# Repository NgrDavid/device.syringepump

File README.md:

## Harp Syringe Pump
This is a repository for the Harp Syringe Pump. The Harp Syringe Pump is a device that can be used to control the flow of liquid through a syringe by driving a stepper motor.

### Key Features ###

* Low and High-level interface control of the stepper motor
* General digital inputs configurable to trigger hardware events
* Digital outputs configurable to report hardware events
* Includes on-board stepper-motor driver
* Included mechanical designs and assembly instructions

### Connectivity ###

* 1x clock sync input (CLKIN) [stereo jack]
* 1x USB (for computer) [USB type B]
* 1x 12V supply [barrel connector jack]
* General purpose I/O (5V) [screw terminal]

## Interface ##

The interface with the Harp Behavior can be done through [Bonsai](https://bonsai-rx.org/) or a dedicated GUI (Graphical User Interface).

## Licensing ##

Each subdirectory will contain a license or, possibly, a set of licenses if it involves both hardware and software.

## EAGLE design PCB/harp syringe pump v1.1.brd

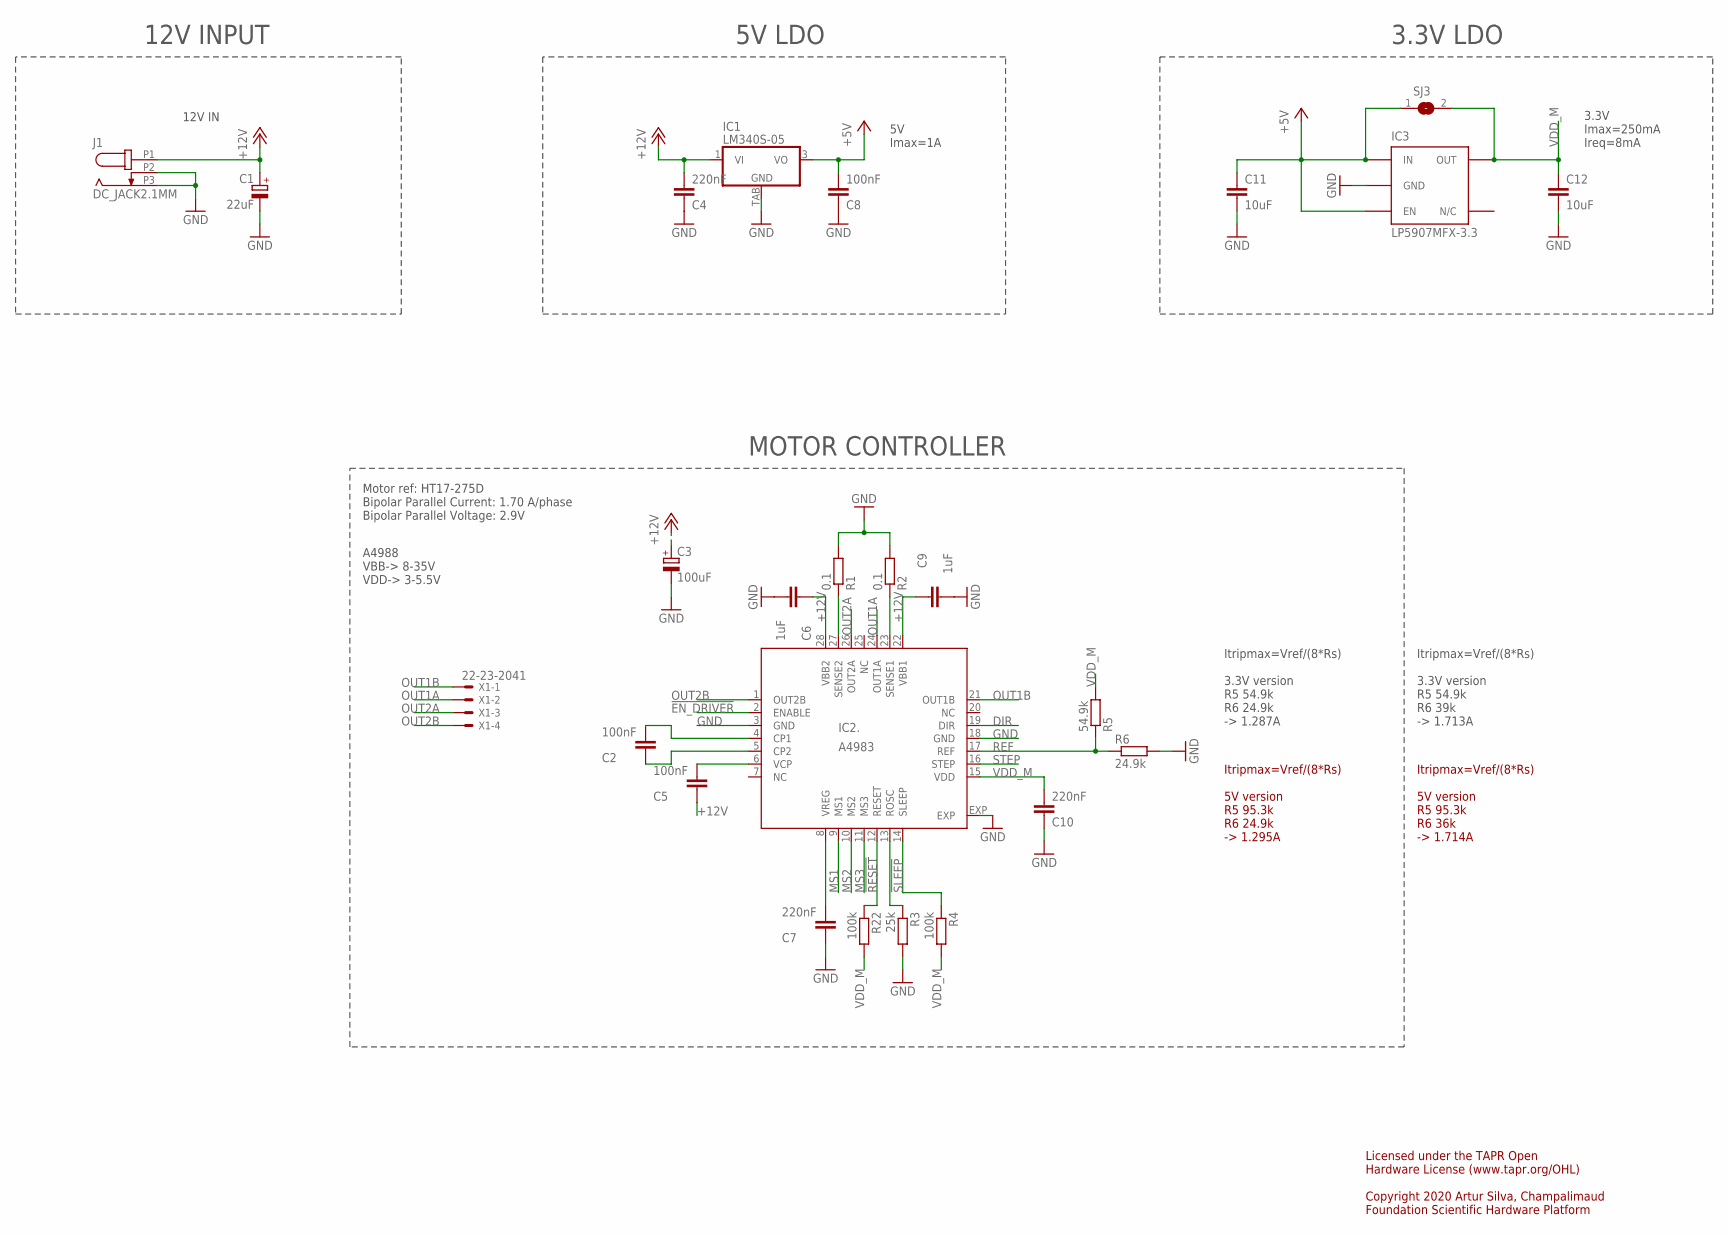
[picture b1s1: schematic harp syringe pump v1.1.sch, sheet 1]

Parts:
C1: 22uF; CAP_100UF_HAND
C2, C5: 100nF; C0603
C3: 100uF; PANASONIC_E
C4, C7, C10: 220nF; C0603
C6, C9: 1uF; C0603
C8: 100nF; C0402
C11, C12: 10uF; C0603
IC1: LM340S-05; TO263-3
IC2.: A4983; QFN28ET
IC3: LP5907MFX-3.3; TSOT23-5
J1: DC_JACK2.1MM; DC_POWER_INPUT_2.1MM
R1, R2: 0.1; R2010
R3: 25k; R0402
R4, R22: 100k; R0402
R5: 54.9k; R0402
R6: 24.9k; R0402
SJ3: SJ
X1: 22-23-2041

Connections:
!EN_DRIVER: IC2..2 (ENABLE); also elsewhere on the board
!RESET: IC2..12 (RESET), R22.1; also elsewhere on the board
!SLEEP: IC2..14 (SLEEP), R4.1; also elsewhere on the board
+5V: C8.2, C11.1, IC1.3 (VO), IC3.1 (IN), IC3.3 (EN), SJ3.1; also elsewhere on the board
+12V: C1.+, C3.+, C4.2, C5.1, C6.1, C9.1, IC1.1 (VI), IC2..22 (VBB1), IC2..28 (VBB2), J1.P1 (1)
CP1: C2.2, IC2..4 (CP1)
CP2: C2.1, IC2..5 (CP2)
DIR: IC2..19 (DIR); also elsewhere on the board
GND: C1.-, C3.-, C4.1, C6.2, C7.1, C8.1, C9.2, C10.1, C11.2, C12.2, IC1.TAB (GND), IC2..3 (GND), IC2..18 (GND), IC2..EXP, IC3.2 (GND), J1.P2 (2), J1.P3 (3), R1.2, R2.2, R3.2, R6.2; also elsewhere on the board
MS1: IC2..9 (MS1); also elsewhere on the board
MS2: IC2..10 (MS2); also elsewhere on the board
MS3: IC2..11 (MS3); also elsewhere on the board
unnamed: C7.2, IC2..8 (VREG)
unnamed: IC2..13 (ROSC), R3.1
OUT1A: IC2..24 (OUT1A), X1.2
OUT1B: IC2..21 (OUT1B), X1.1
OUT2A: IC2..26 (OUT2A), X1.3
OUT2B: IC2..1 (OUT2B), X1.4
REF: IC2..17 (REF), R5.1, R6.1
SENSE1: IC2..23 (SENSE1), R2.1
SENSE2: IC2..27 (SENSE2), R1.1
STEP: IC2..16 (STEP); also elsewhere on the board
VCP: C5.2, IC2..6 (VCP)
VDD_M: C10.2, C12.1, IC2..15 (VDD), IC3.5 (OUT), R4.2, R5.2, R22.2, SJ3.2

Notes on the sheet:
Licensed under the TAPR Open Hardware License (www.tapr.org/OHL) Copyright 2020 Artur Silva, Champalimaud Foundation Scientific Hardware Platform
12V IN
3.3V Imax=250mA Ireq=8mA
MOTOR CONTROLLER
Motor ref: HT17-275D Bipolar Parallel Current: 1.70 A/phase Bipolar Parallel Voltage: 2.9V
5V LDO
3.3V LDO
12V INPUT
A4988 VBB-> 8-35V VDD-> 3-5.5V
5V Imax=1A
Itripmax=Vref/(8*Rs) 3.3V version R5 54.9k R6 24.9k -> 1.287A
Itripmax=Vref/(8*Rs) 5V version R5 95.3k R6 24.9k -> 1.295A
Itripmax=Vref/(8*Rs) 5V version R5 95.3k R6 36k -> 1.714A
Itripmax=Vref/(8*Rs) 3.3V version R5 54.9k R6 39k -> 1.713A

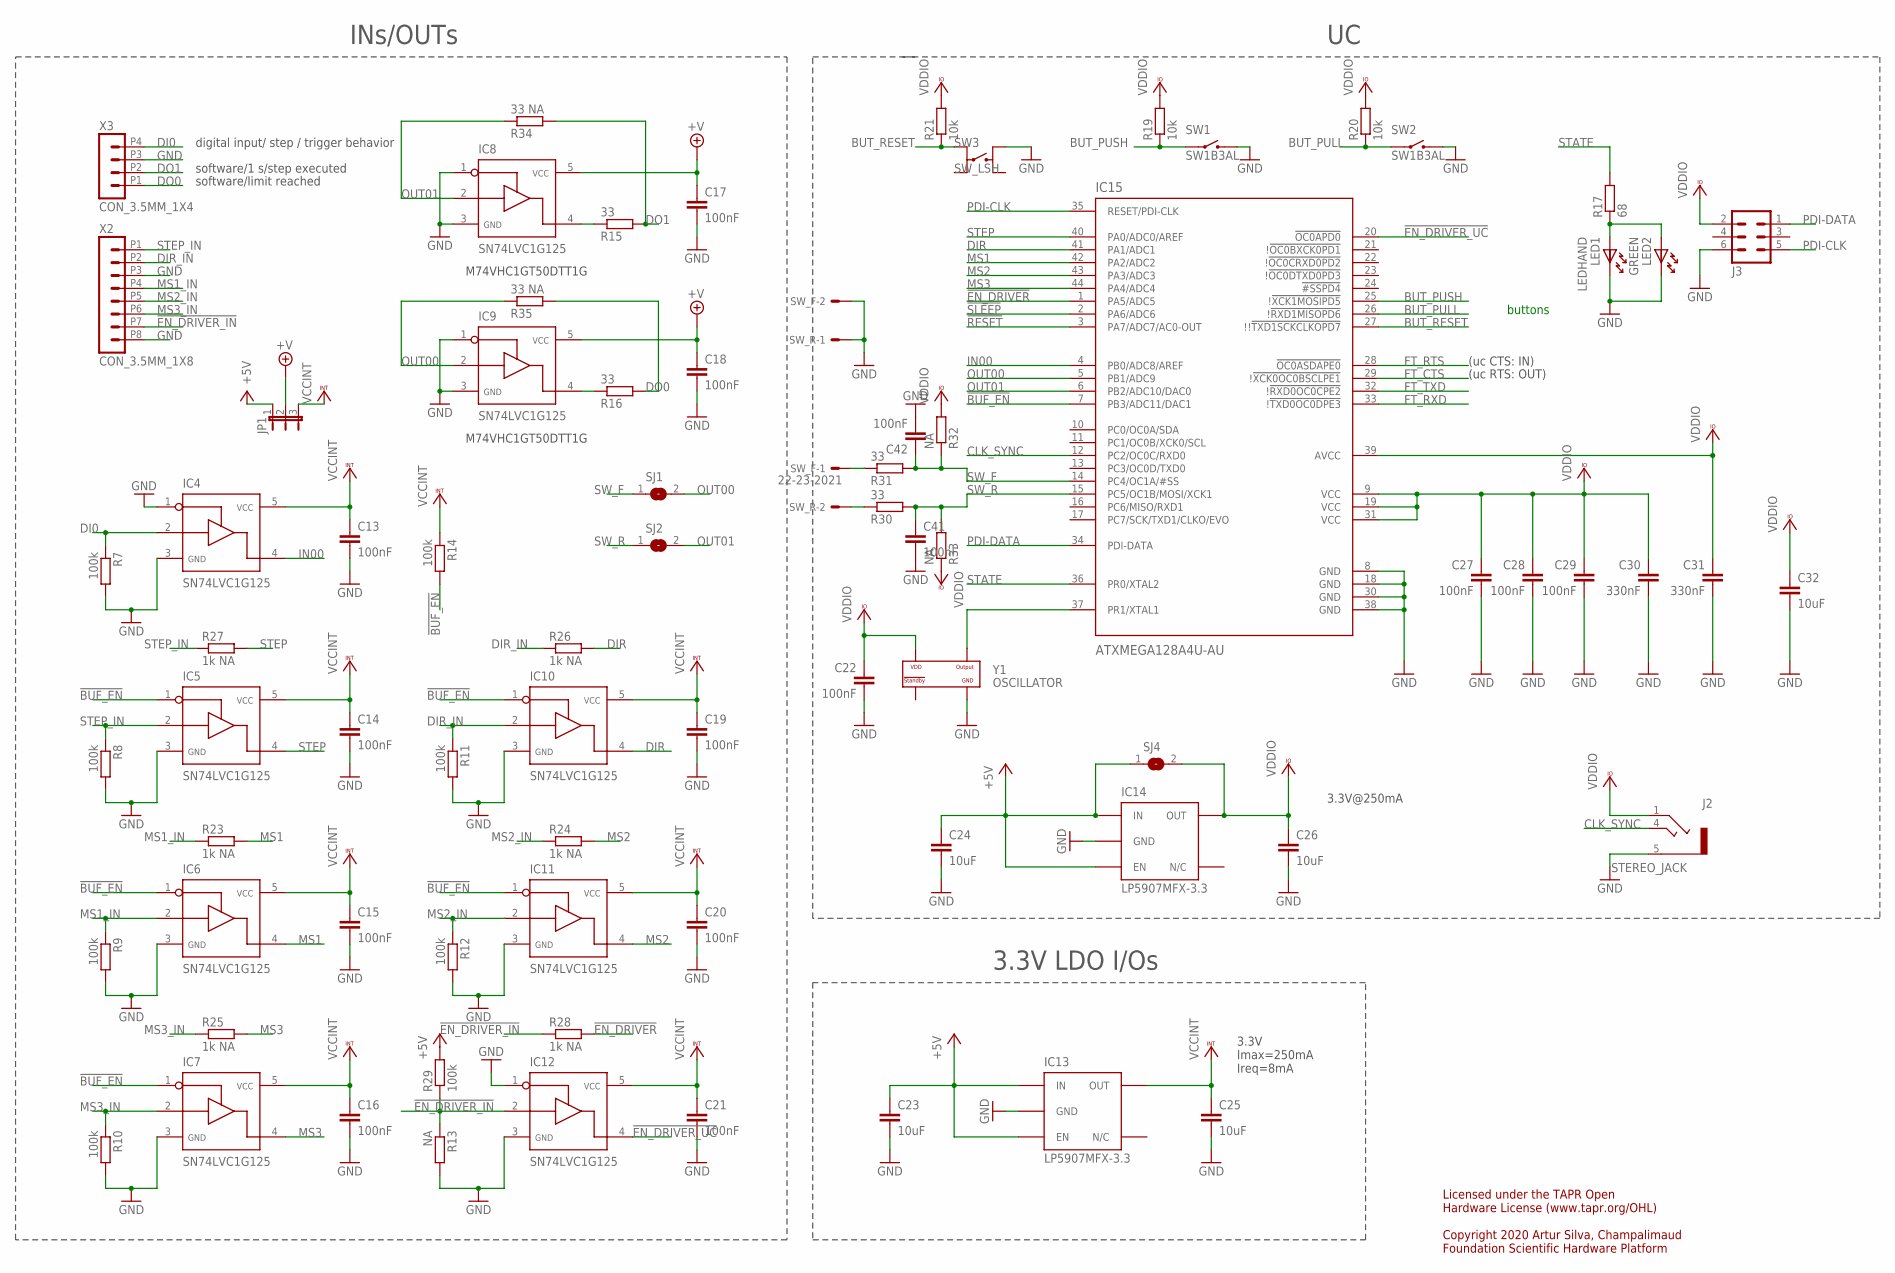
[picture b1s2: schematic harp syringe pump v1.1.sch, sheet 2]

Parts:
C13, C14, C15, C16, C17, C18, C19, C20, C21, C22, C27, C28, C29, C41, C42: 100nF; C0402
C23, C24, C25, C26, C32: 10uF; C0603
C30, C31: 330nF; C0402
IC4, IC5, IC6, IC7, IC8, IC9, IC10, IC11, IC12: SN74LVC1G125; SOT23-5
IC13, IC14: LP5907MFX-3.3; TSOT23-5
IC15: ATXMEGA128A4U-AU; QFP80P1200X1200X120-44N
J2: STEREO_JACK; 35RASMT2BHNTRX
J3: MA03-2
JP1: JP2E; JP2
LED1: LEDHAND; LED_HAND
LED2: GREEN; LED_HAND
R7, R8, R9, R10, R11, R12, R14, R29: 100k; R0402
R13, R32, R33: NA; R0402
R15, R16, R30, R31: 33; R0402
R17: 68; R0402
R19, R20, R21: 10k; R0402
R23, R24, R25, R26, R27, R28: 1k NA; R0402
R34, R35: 33 NA; R0402
SJ1, SJ2, SJ4: SJ
SW1, SW2: SW1B3AL; SW_B3AL
SW3: SW_LSH; SWITCH_LSH
SW_F: 22-23-2021
SW_R: 22-23-2021
X2: CON_3.5MM_1X8
X3: CON_3.5MM_1X4
Y1: OSCILLATOR; OSCILLATOR_3.2X2.5

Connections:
!BUF_EN: IC5.1, IC6.1, IC7.1, IC10.1, IC11.1, IC15.7 (PB3/ADC11/DAC1), R14.2
!EN_DRIVER: IC15.1 (PA5/ADC5), R28.2; also elsewhere on the board
!EN_DRIVER_IN: IC12.2, R13.1, R28.1, R29.1, X2.P7 (7)
!EN_DRIVER_UC: IC12.4, IC15.20 (!OC0APD0)
!RESET: IC15.3 (PA7/ADC7/AC0-OUT); also elsewhere on the board
!SLEEP: IC15.2 (PA6/ADC6); also elsewhere on the board
+5V: C23.1, C24.1, IC13.1 (IN), IC13.3 (EN), IC14.1 (IN), IC14.3 (EN), JP1.1, R29.2, SJ4.1; also elsewhere on the board
+V: C17.1, C18.1, IC8.5, IC9.5, JP1.2
BUT_PULL: IC15.26 (!!RXD1MISOPD6), R20.1, SW2.P
BUT_PUSH: IC15.25 (!!XCK1MOSIPD5), R19.1, SW1.P
BUT_RESET: IC15.27 (!!!TXD1SCKCLKOPD7), R21.1, SW3.P0
CLK_SYNC: IC15.12 (PC2/OC0C/RXD0), J2.4
DI0: IC4.2, R7.1, X3.P4 (4)
DIR: IC10.4, IC15.41 (PA1/ADC1), R26.2; also elsewhere on the board
DIR_IN: IC10.2, R11.1, R26.1, X2.P2 (2)
DO0: R16.2, R35.2, X3.P1 (1)
DO1: R15.2, R34.2, X3.P2 (2)
FT_CTS: IC15.29 (!!XCK0OC0BSCLPE1); also elsewhere on the board
FT_RTS: IC15.28 (!OC0ASDAPE0); also elsewhere on the board
FT_RXD: IC15.33 (!!TXD0OC0DPE3); also elsewhere on the board
FT_TXD: IC15.32 (!!RXD0OC0CPE2); also elsewhere on the board
GND: C13.2, C14.2, C15.2, C16.2, C17.2, C18.2, C19.2, C20.2, C21.2, C22.2, C23.2, C24.2, C25.2, C26.2, C27.2, C28.2, C29.2, C30.2, C31.2, C32.2, C41.2, C42.2, IC4.1, IC4.3, IC5.3, IC6.3, IC7.3, IC8.1, IC8.3, IC9.1, IC9.3, IC10.3, IC11.3, IC12.1, IC12.3, IC13.2 (GND), IC14.2 (GND), IC15.8 (GND), IC15.18 (GND), IC15.30 (GND), IC15.38 (GND), J2.5, J3.6, LED1.K, LED2.K, R7.2, R8.2, R9.2, R10.2, R11.2, R12.2, R13.2, SW1.O, SW2.O, SW3.O0 (O), SW_F.2, SW_R.1, X2.P3 (3), X2.P8 (8), X3.P3 (3), Y1.P$2 (GND); also elsewhere on the board
IN00: IC4.4, IC15.4 (PB0/ADC8/AREF)
MS1: IC6.4, IC15.42 (PA2/ADC2), R23.2; also elsewhere on the board
MS1_IN: IC6.2, R9.1, R23.1, X2.P4 (4)
MS2: IC11.4, IC15.43 (PA3/ADC3), R24.2; also elsewhere on the board
MS2_IN: IC11.2, R12.1, R24.1, X2.P5 (5)
MS3: IC7.4, IC15.44 (PA4/ADC4), R25.2; also elsewhere on the board
MS3_IN: IC7.2, R10.1, R25.1, X2.P6 (6)
unnamed: IC8.4, R15.1
unnamed: R30.1, SW_R.2
unnamed: R31.1, SW_F.1
unnamed: IC9.4, R16.1
unnamed: LED1.A, LED2.A, R17.1
OSC1: IC15.37 (PR1/XTAL1), Y1.P$3 (OUTPUT)
OUT00: IC9.2, IC15.5 (PB1/ADC9), R35.1, SJ1.2
OUT01: IC8.2, IC15.6 (PB2/ADC10/DAC0), R34.1, SJ2.2
PDI-CLK: IC15.35 (RESET/PDI-CLK), J3.5
PDI-DATA: IC15.34 (PDI-DATA), J3.1
STATE: IC15.36 (PR0/XTAL2), R17.2
STEP: IC5.4, IC15.40 (PA0/ADC0/AREF), R27.2; also elsewhere on the board
STEP_IN: IC5.2, R8.1, R27.1, X2.P1 (1)
SW_F: C42.1, IC15.14 (PC4/OC1A/#SS), R31.2, R32.1, SJ1.1
SW_R: C41.1, IC15.15 (PC5/OC1B/MOSI/XCK1), R30.2, R33.2, SJ2.1
VCCINT: C13.1, C14.1, C15.1, C16.1, C19.1, C20.1, C21.1, C25.1, IC4.5, IC5.5, IC6.5, IC7.5, IC10.5, IC11.5, IC12.5, IC13.5 (OUT), JP1.3, R14.1
VCCIO: C22.1, C26.1, C27.1, C28.1, C29.1, C30.1, C31.1, C32.1, IC14.5 (OUT), IC15.9 (VCC), IC15.19 (VCC), IC15.31 (VCC), IC15.39 (AVCC), J2.1, J3.2, R19.2, R20.2, R21.2, R32.2, R33.1, SJ4.2, Y1.P$4 (VDD)

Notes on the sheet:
3.3V@250mA
(uc CTS: IN)
(uc RTS: OUT)
buttons
M74VHC1GT50DTT1G
INs/OUTs
digital input/ step / trigger behavior
software/1 s/step executed
software/limit reached
3.3V Imax=250mA Ireq=8mA
3.3V LDO I/Os
Licensed under the TAPR Open Hardware License (www.tapr.org/OHL) Copyright 2020 Artur Silva, Champalimaud Foundation Scientific Hardware Platform

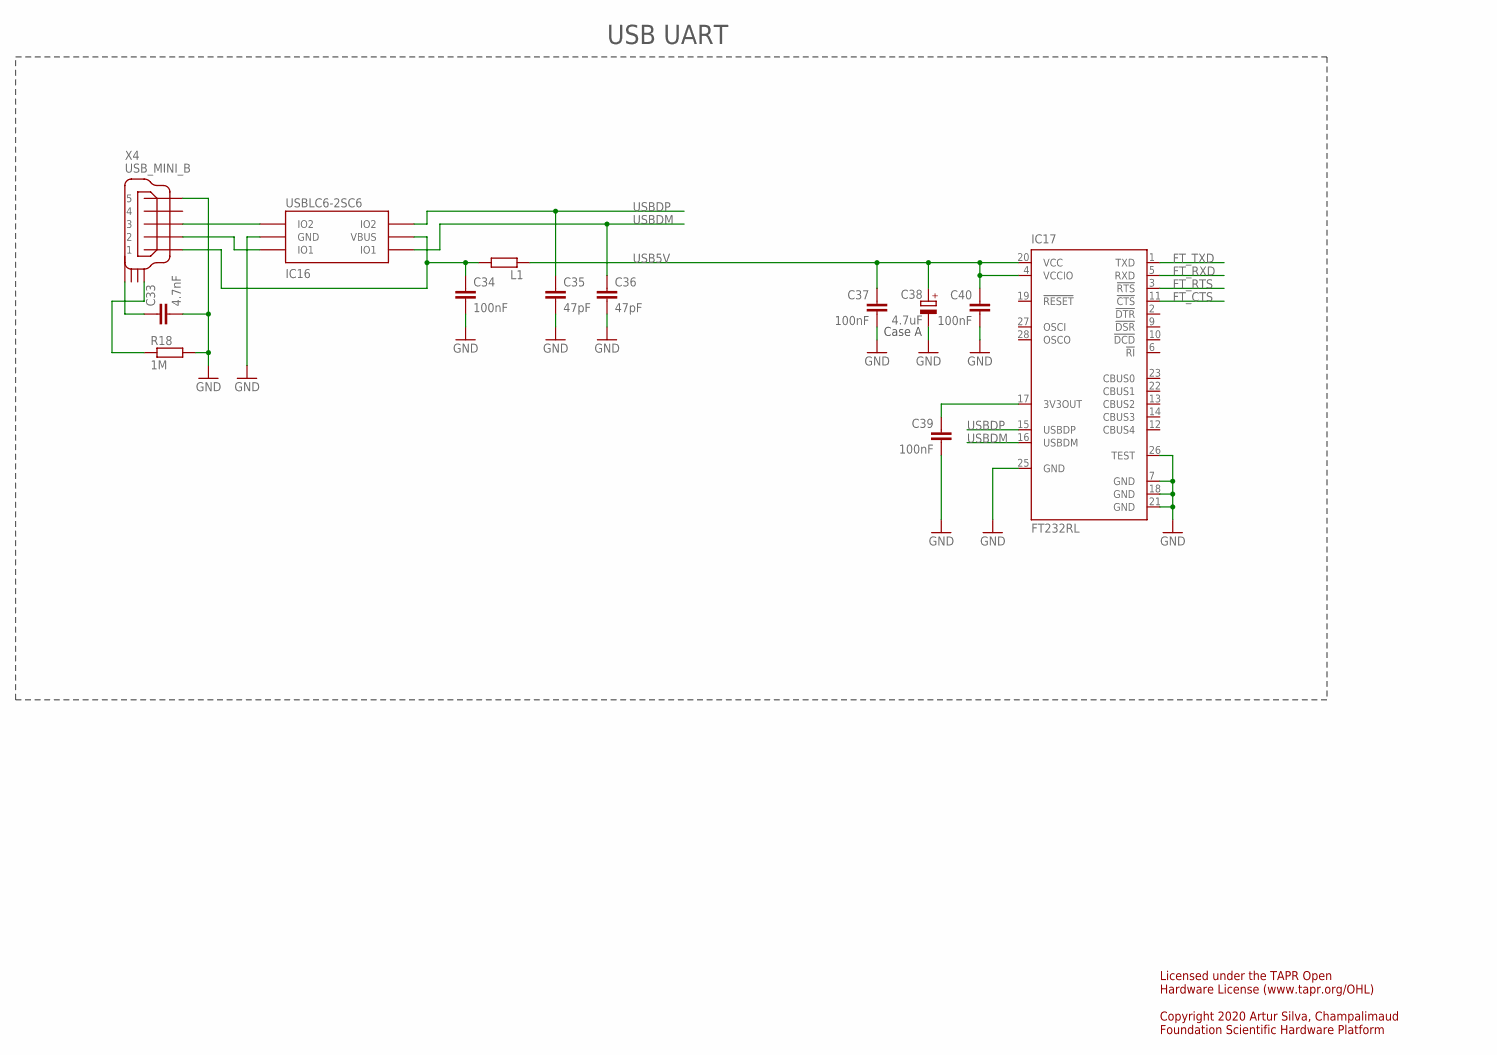
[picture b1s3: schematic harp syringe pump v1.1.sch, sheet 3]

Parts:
C33: 4.7nF; C0402
C34, C37, C39, C40: 100nF; C0402
C35, C36: 47pF; C0402
C38: 4.7uF; A/3216-18W
IC16: USBLC6-2SC6; SOT23-6L
IC17: FT232RL; SSOP28
L1: ???; R0805
R18: 1M; R0402
X4: USB_MINI_B; 240-0002-1

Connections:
3V3OUT: C39.1, IC17.17 (3V3OUT)
FT_CTS: IC17.11 (!CTS); also elsewhere on the board
FT_RTS: IC17.3 (!RTS); also elsewhere on the board
FT_RXD: IC17.5 (RXD); also elsewhere on the board
FT_TXD: IC17.1 (TXD); also elsewhere on the board
GND: C33.2, C34.2, C35.2, C36.2, C37.2, C38.-, C39.2, C40.2, IC16.P$2 (GND), IC17.7 (GND), IC17.18 (GND), IC17.21 (GND), IC17.25 (GND), IC17.26 (TEST), R18.2, X4.P$5 (5); also elsewhere on the board
unnamed: IC16.P$3 (IO2), X4.P$3 (3)
unnamed: C33.1, X4.SHIELD_4
unnamed: C34.1, IC16.P$5 (VBUS), L1.2, X4.P$1 (1)
unnamed: R18.1, X4.SHIELD_1
unnamed: IC16.P$1 (IO1), X4.P$2 (2)
USB5V: C37.1, C38.+, C40.1, IC17.4 (VCCIO), IC17.20 (VCC), L1.1
USBDM: C36.1, IC16.P$6 (IO1), IC17.16 (USBDM)
USBDP: C35.1, IC16.P$4 (IO2), IC17.15 (USBDP)

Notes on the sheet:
Case A
USB UART
Licensed under the TAPR Open Hardware License (www.tapr.org/OHL) Copyright 2020 Artur Silva, Champalimaud Foundation Scientific Hardware Platform

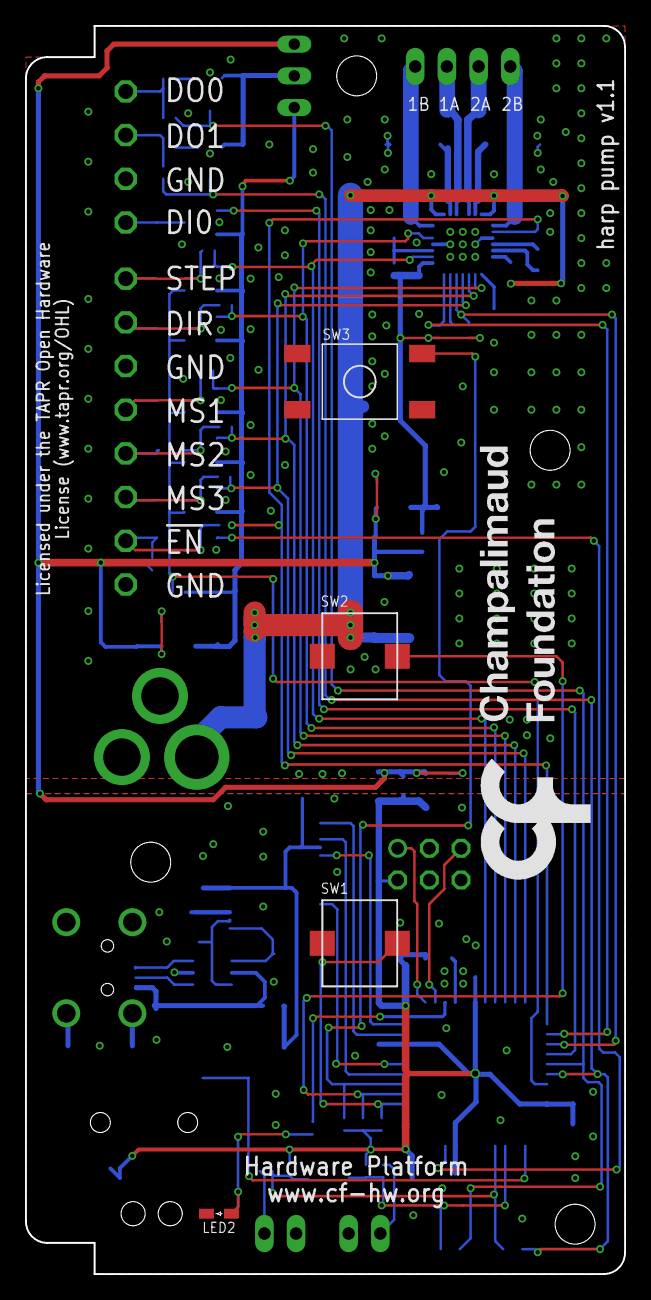
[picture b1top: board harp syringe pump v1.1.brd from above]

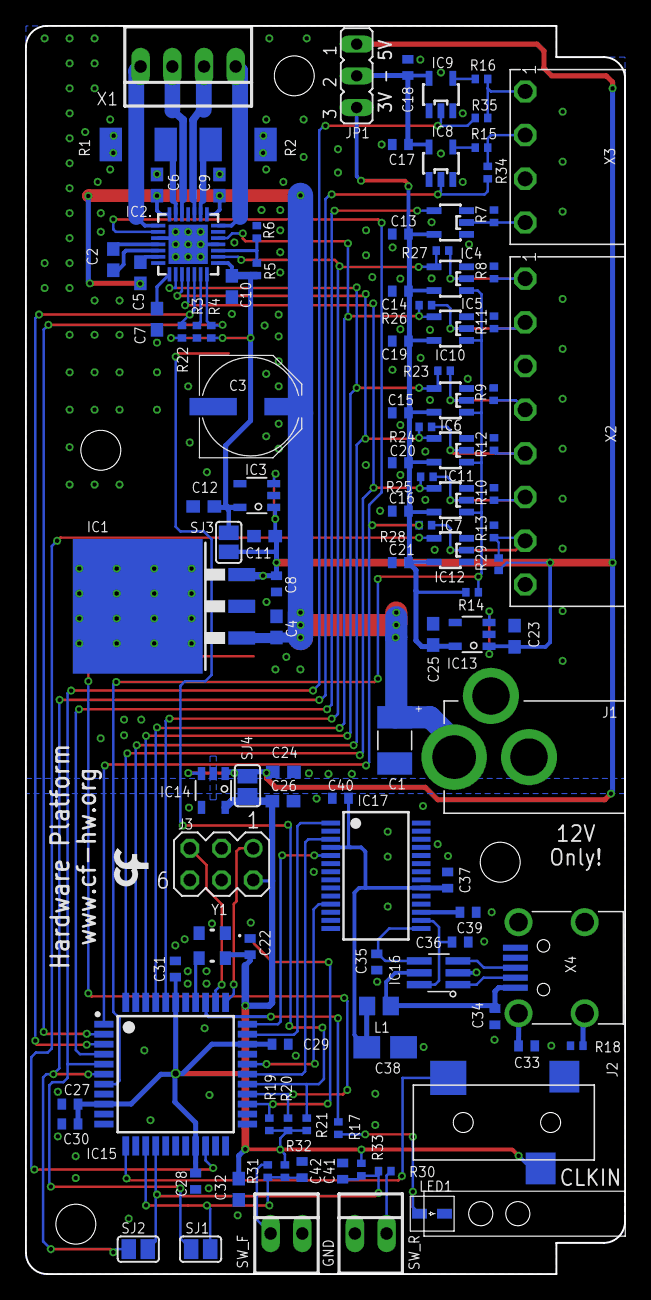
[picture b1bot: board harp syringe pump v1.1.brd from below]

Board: 2 copper layers, 48.0 x 100.0 mm, 118 parts (113 on the bottom side), 69 nets.

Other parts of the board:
U$2: LOGO_5
U$3: LED_PIPE_7513D2-L
U$4: LOGO_8

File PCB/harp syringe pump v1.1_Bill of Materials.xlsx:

| Part(s) | Quantity Low Level | Quantity Full | Description | Distributor | Part. No.
 | IC1 | 1 | 1 | Reguladores de tensão linear 3-TERMINAL POS REG 5V 1A | Mouser | 926-LM340S-5.0/NOPB |  | Low Level Only Bold
 | IC2 | 1 | 1 | DMOS Microstepping Driver with Translator and Overcurrent Protection IC | Farnell | 2057418
 | IC3, IC13, IC14 | 0 | 3 | LDO 250mA Ultra-Lo Noise LDO Reg | Mouser | 595-LP5907MFX-3.3NPB
 | IC4, IC5, IC6, IC7, IC10, IC11, IC12 | 0 | 7 | SingleBuffer / Driver, 1.65V to 5.5V, SOT-23-5 | Mouser | 595-SN74LVC1G125DBVR
 | IC8, IC9 | 0 | 2 | Buffers e line drivers 1.65-5.5V Single Non-Inverting TTL | Mouser | 863-M74VHC1GT50DTT1G
 | IC15 | 0 | 1 | Microcontroladores de 8 bits - MCU 44TQFP, IND TEMP GREEN, 1.6-3.6V | Mouser | 556-ATXMEGA128A4U-AU
 | IC16 | 0 | 1 | ESD Protection Low Cap | Mouser | 511-USBLC6-2SC6Y
 | IC17 | 0 | 1 | IC USB USB to Serial UART Enhanced IC SSOP-28 | Mouser | 895-FT232RL
 | C35, C36 | 0 | 2 | CAP CER 47pF 50V ±5% C0G 0402 | Mouser | 77-VJ0402A470JXACBC
 | C33 | 0 | 1 | CAP CER 4.7nF 100V ±10% X7R 0402 | Mouser | 81-GRM155R72A472KA01
 | C13, C14, C15, C16, C17, C18, C19, C20, C21, C22, C27, C28, C29, C34, C37, C39,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 | 2 | 19 | CAP CER 100nF 10V ±10% X5R 0402 | Farnell | 2310530
 | C2, C5, C8 | 3 | 3 | CAP CER 100nF 100V ±10% X7R 0402 | Mouser | 81-GRM188R72A104KA35
 | C4, C7, C10 | 3 | 3 | CAP CER 220nF 100V ±10% X7R 0603 | Mouser | 81-GCM188R71H224KA4J
 | C30, C31 | 0 | 2 | CAP CER 330nF 10V ±10% X5R 0402 | Digikey | CL05A334KP5NNNC
 | C6, C9 | 2 | 2 | CAP CER 1uF 25V ±20% X5R 0603 | Mouser | 581-06033D105K
 | C38 | 0 | 1 | CAP TAN 4.7uF 10V ±10% 1206 | Mouser | 80-T491A475K107280
 | C11, C12, C23, C24, C25, C26, C32 | 1 | 7 | CAP CER 10uF 35V ±20% X5R 0603 | Mouser | 81-GRM188R6YA106MA3D
 | C1 | 1 | 1 | CAP TAN 22uF 20V ±10% 1210 | Mouser | 667-20TQC22MYFB
 | C3 | 1 | 1 | CAP ELE 100uF 25V ±20% | Mouser | 667-EEE-FK1E101P
 | R1, R2 | 2 | 2 | RES SMD 0.1Ω 1% 2010 1W | Mouser | 652-CRM2010FXR100ELF
 | R15, R16, R30, R31 | 2 | 4 | RES SMD 33Ω ±5% 0402 | Mouser | 667-ERJ-2GEJ330X
 | R34, R35 | 2 | 0 | RES SMD 33Ω ±5% 0402 | Mouser | 667-ERJ-2GEJ330X
 | R17 | 0 | 1 | RES SMD 68Ω 5% 0402 | Mouser | 71-CRCW0402-68-E3
 | R23, R24, R25, R26, R27, R28 | 6 | 0 | RES SMD 1kΩ 1% 0402 | Mouser | 667-ERJ-2RKF1001X
 | R19, R20, R21 | 0 | 3 | RES SMD 10kΩ 1% 0402 | Mouser | 667-ERJ-2RKF1002X
 | R32, R33 | 2 | 0 | RES SMD 10kΩ 1% 0402 | Mouser | 667-ERJ-2RKF1002X
 | R3 | 1 | 1 | RES SMD 24.9kΩ 1% 0402 | Mouser | 667-ERJ-2RKF2492X
 | R6 | 0 | 1 | RES SMD 39kΩ 1% 0402 | Mouser | 667-ERJ-2RKF3902X
 | R6 | 1 | 0 | RES SMD 36kΩ 1% 0402 | Mouser | 667-ERJ-2RKF3602X
 | R5 | 0 | 1 | RES SMD 54.9kΩ 1% 0402 | Mouser | 667-ERJ-U02F5492X
 | R5 | 1 | 0 | RES SMD 95.3kΩ 1% 0402 | Mouser | ERJ-U02F9532X
 | R4, R7, R8, R9, R10, R11, R12, R14, R22, R29 | 2 | 10 | RES SMD 100kΩ ±1% 0402 | Mouser | 667-ERJ-2RKF1003X
 | R18 | 0 | 1 | RES SMD 1MΩ 1% 0402 | Mouser | 652-CR0402FX-1004GLF
 | LED1 | 0 | 1 | LED, Green, 1.6mm x 0.8mm, 566 nm, 2.1 V, 20 mA, 15 mcd | Mouser | 78-TLMP1100-GS08
 | SW1 | 0 | 1 | Interruptores táteis 2.45N OF Long Stroke Green Button | Mouser | 653-B3AL-1001P
 | SW2 | 0 | 1 | Interruptores táteis 1.96N OF Long Stroke Red Button | Mouser | 653-B3AL-1000P
 | Y1 | 0 | 1 | 32MHz 10ppm | Mouser | 998-1001CI5032.0000T
 | J2 | 0 | 1 | SMT 3.5 STEREO REEL | Mouser | 502-35RASMT2BHNTRX
 | L1 | 0 | 1 | 40ohms 100MHz 1.5A Monolithic 0805 SMD | Mouser | 875-MI0805K400R-10
 | J3 | 0 | 1 | 6P DR UNSHRD HRD | Mouser | 649-67996-206HLF
 | X4 | 0 | 1 | UX60-MB-5S8 | Mouser | 798-UX60-MB-5S8
 | USB Cable | 0 | 1 | USB A - MINI-B 0.8M - MINI-B 0.8M BLACK | Mouser | 538-88732-8502
 |  | 0 | 1 | Tubos de Luz LED CML LIGHTPIPE | Mouser | 606-7513D2-L
 | JP1 | 0 | 1 | 3POS HDR 15AU | Mouser | 649-68001-203HLF
 |  | 0 | 1 | Distribuidores e Alojamento de Fios JUMPER SKT BLACK OPEN TOP | Mouser | 855-M7582-46
 | J1 | 1 | 1 | CC PCB 2.1MM | Mouser | 163-179PH-EX
 | SW_LIMITERS | 2 | 2 | SWITCH SNAP ACT SPST-NC 5A 125V | Mouser | 653-SS5GL22T
 | WALL ADAPTER | 1 | 1 | AC/DC Power Supply, Class II, Fixed, 1 Output, 90 V, 264 V, 12 W, 12 V | Farnell | VEL12US120-EU-JA
 | X1 | 1 | 1 | Wire-To-Board Terminal Block, 2.54 mm, 4 Ways, 30 AWG, 16 AWG, 1.4 mm², Screw | Farnell | 282834-4
 |  | 1 | 1 | 20.1550M/4-E - Pluggable Terminal Block, 3.5 mm, 4 Ways | Farnell | 2575217
 |  | 1 | 1 | 20.1550M/8-E - Pluggable Terminal Block, 3.5 mm, 8 Ways | Farnell | 2575220
 | X3 | 1 | 1 | Horizontal, Header, 3.5 mm, 4 Ways, 10 A, 250 V, Through Hole Right Angle | Farnell | 20.155MH/4-E
 | X2 | 1 | 1 | Horizontal, Header, 3.5 mm, 8 Ways, 10 A, 250 V, Through Hole Right Angle | Farnell | 20.155MH/8-E
 |  | 1 | 1 | Heat Sink, Black Anodised, 87 °C/W, For DIP, PLCC, SMD, 4.8mm/6.3mm/8mm | Farnell | 4302175
 |  | 1 | 1 | Thermal Conductive Foil, 0.37 W/m.K | Farnell | 1211706
 |  | 2 | 2 | Blocos de terminais fixos 2P SIDE ENTRY 2.54mm | Mouser | 571-282834-2
 | SJ1, SJ2, SJ3, SJ4 | 4 | 4 | - | - | -
 | Components | 51 | 112
 | PCB |  |  | 100mmx48mm 5x 2layers 35um
 | Licensed under the TAPR Open Hardware License (www.tapr.org/OHL)
 | Copyright 2020 Artur Silva, Champalimaud Foundation Scientific Hardware Platform

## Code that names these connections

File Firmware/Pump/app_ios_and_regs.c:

#include <avr/io.h>
#include "hwbp_core_types.h"
#include "app_ios_and_regs.h"

/************************************************************************/
/* Configure and initialize IOs                                         */
/************************************************************************/
void init_ios(void)
{	/* Configure input pins */
	io_pin2in(&PORTB, 0, PULL_IO_TRISTATE, SENSE_IO_EDGES_BOTH);         // IN00
	io_pin2in(&PORTC, 0, PULL_IO_DOWN, SENSE_IO_EDGES_BOTH);             // TYPE0
	io_pin2in(&PORTC, 1, PULL_IO_DOWN, SENSE_IO_EDGES_BOTH);             // TYPE1
	io_pin2in(&PORTC, 4, PULL_IO_UP, SENSE_IO_EDGES_BOTH);               // SW_F
	io_pin2in(&PORTC, 5, PULL_IO_UP, SENSE_IO_EDGES_BOTH);               // SW_R
	io_pin2in(&PORTD, 0, PULL_IO_TRISTATE, SENSE_IO_EDGES_BOTH);         // EN_DRIVER_UC
	io_pin2in(&PORTD, 5, PULL_IO_UP, SENSE_IO_EDGES_BOTH);               // BUT_PUSH
	io_pin2in(&PORTD, 6, PULL_IO_UP, SENSE_IO_EDGES_BOTH);               // BUT_PULL
	io_pin2in(&PORTD, 7, PULL_IO_UP, SENSE_IO_EDGES_BOTH);               // BUT_RESET

	/* Configure input interrupts */
	io_set_int(&PORTB, INT_LEVEL_LOW, 0, (1<<0), false);                 // IN00
	io_set_int(&PORTC, INT_LEVEL_LOW, 0, (1<<0), false);                 // TYPE0
	io_set_int(&PORTC, INT_LEVEL_LOW, 0, (1<<1), false);                 // TYPE1
	io_set_int(&PORTC, INT_LEVEL_LOW, 0, (1<<4), false);                 // SW_F
	io_set_int(&PORTC, INT_LEVEL_LOW, 0, (1<<5), false);                 // SW_R
	io_set_int(&PORTD, INT_LEVEL_LOW, 0, (1<<0), false);                 // EN_DRIVER_UC
	io_set_int(&PORTD, INT_LEVEL_LOW, 0, (1<<5), false);                 // BUT_PUSH
	io_set_int(&PORTD, INT_LEVEL_LOW, 0, (1<<6), false);                 // BUT_PULL
	io_set_int(&PORTD, INT_LEVEL_LOW, 0, (1<<7), false);                 // BUT_RESET

	/* Configure output pins */
	io_pin2out(&PORTA, 0, OUT_IO_DIGITAL, IN_EN_IO_EN);                  // STEP
	io_pin2out(&PORTA, 1, OUT_IO_DIGITAL, IN_EN_IO_EN);                  // DIR
	io_pin2out(&PORTA, 2, OUT_IO_DIGITAL, IN_EN_IO_DIS);                 // MS1
	io_pin2out(&PORTA, 3, OUT_IO_DIGITAL, IN_EN_IO_DIS);                 // MS2
	io_pin2out(&PORTA, 4, OUT_IO_DIGITAL, IN_EN_IO_DIS);                 // MS3
	io_pin2out(&PORTA, 5, OUT_IO_DIGITAL, IN_EN_IO_EN);                  // EN_DRIVER
	io_pin2out(&PORTA, 6, OUT_IO_DIGITAL, IN_EN_IO_DIS);                 // SLEEP
	io_pin2out(&PORTA, 7, OUT_IO_DIGITAL, IN_EN_IO_DIS);                 // RESET
	io_pin2out(&PORTB, 1, OUT_IO_DIGITAL, IN_EN_IO_EN);                  // OUT00
	io_pin2out(&PORTB, 2, OUT_IO_DIGITAL, IN_EN_IO_EN);                  // OUT01
	io_pin2out(&PORTB, 3, OUT_IO_DIGITAL, IN_EN_IO_DIS);                 // BUF_EN

	/* Initialize output pins */
	clr_STEP;
	clr_DIR;
	clr_MS1;
	clr_MS2;
	clr_MS3;
	set_EN_DRIVER;
	set_SLEEP;
	set_RESET;
	clr_OUT00;
	clr_OUT01;
	set_BUF_EN;
}

/************************************************************************/
/* Registers' stuff                                                     */
/************************************************************************/
AppRegs app_regs;

uint8_t app_regs_type[] = {
	TYPE_U8,
	TYPE_U8,
	TYPE_U8,
	TYPE_U8,
	TYPE_U8,
	TYPE_U8,
	TYPE_U8,
	TYPE_U8,
	TYPE_U8,
	TYPE_U8,
	TYPE_U8,
	TYPE_U8,
	TYPE_U8,
	TYPE_U16,
	TYPE_FLOAT,
	TYPE_U16,
	TYPE_FLOAT,
	TYPE_U8,
	TYPE_U8,
	TYPE_U8,
	TYPE_U8,
	TYPE_U8,
	TYPE_U8,
	TYPE_U8
};

uint16_t app_regs_n_elements[] = {
	1,
	1,
	1,
	1,
	1,
	1,
	1,
	1,
	1,
	1,
	1,
	1,
	1,
	1,
	1,
	1,
	1,
	1,
	1,
	1,
	1,
	1,
	1,
	1
};

uint8_t *app_regs_pointer[] = {
	(uint8_t*)(&app_regs.REG_ENABLE_MOTOR_DRIVER),
	(uint8_t*)(&app_regs.REG_START_PROTOCOL),
	(uint8_t*)(&app_regs.REG_STEP_STATE),
	(uint8_t*)(&app_regs.REG_DIR_STATE),
	(uint8_t*)(&app_regs.REG_SW_FORWARD_STATE),
	(uint8_t*)(&app_regs.REG_SW_REVERSE_STATE),
	(uint8_t*)(&app_regs.REG_INPUT_STATE),
	(uint8_t*)(&app_regs.REG_SET_DOS),
	(uint8_t*)(&app_regs.REG_CLEAR_DOS),
	(uint8_t*)(&app_regs.REG_DO0_CONFIG),
	(uint8_t*)(&app_regs.REG_DO1_CONFIG),
	(uint8_t*)(&app_regs.REG_DI0_CONFIG),
	(uint8_t*)(&app_regs.REG_MOTOR_MICROSTEP),
	(uint8_t*)(&app_regs.REG_PROTOCOL_NUMBER_STEPS),
	(uint8_t*)(&app_regs.REG_PROTOCOL_FLOWRATE),
	(uint8_t*)(&app_regs.REG_PROTOCOL_PERIOD),
	(uint8_t*)(&app_regs.REG_PROTOCOL_VOLUME),
	(uint8_t*)(&app_regs.REG_PROTOCOL_TYPE),
	(uint8_t*)(&app_regs.REG_CALIBRATION_VALUE_1),
	(uint8_t*)(&app_regs.REG_CALIBRATION_VALUE_2),
	(uint8_t*)(&app_regs.REG_EVT_ENABLE),
	(uint8_t*)(&app_regs.REG_SET_BOARD_TYPE),
	(uint8_t*)(&app_regs.REG_PROTOCOL_STATE),
	(uint8_t*)(&app_regs.REG_PROTOCOL_DIRECTION)
};

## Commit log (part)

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2020-07-28 add .gitignore
2020-07-28 add LICENSE file
2020-07-28 add initial Firmware project
2020-07-29 init device
2020-07-29 reset registers
2020-07-31 add limit validation for PROTOCOL_NUMBER_STEPS and PROTOCOL_FLOWRATE registers
2020-08-04 update initial PROTOCOL_NUMBER_STEPS
2020-08-04 registers reinitialized
2020-08-04 MOTOR_MICROSTEP register handling
2020-08-04 ENABLE_MOTOR_DRIVER register handling
2020-08-05 add initial motor handling support
2020-08-05 add initial IN0 handling
2020-08-05 add basic DIR handling on motor
2020-08-05 add basic steps disabling on SW_F or SW_R interrupt
2020-08-05 handling of DO1_DATA_SEC option of DO1_CONFIG
2020-08-05 handling of DI0_SYNC option of DI0_CONFIG
2020-08-07 fix ENABLE_MOTOR_DRIVER register handling
2020-08-07 fix mask validation conditions
2020-08-07 fix MOTOR_MICROSTEP register handling
2020-08-07 fix OUT1_STEP_STATE mode handling
2020-08-07 fix masks size
2020-08-07 change SW_F and SW_R to be pull up pins
2020-08-07 fix registers names
2020-08-07 update registers.xls with name, mask fixes and new register
2020-08-07 init new register
2020-08-10 force start counting the step duration on register change
2020-08-10 add ENABLE_MOTOR_UC register handling
2020-08-10 add handling of DI0_RISE_FALL_UPDATE_STEP option of register DI0_CONFIG
2020-08-10 handle EN_DRIVER_UC interrupt
2020-08-10 add initial buttons press detection
2020-08-10 remove unneeded code
2020-08-11 fix initial button press detection
2020-08-17 update code with new registers
2020-08-17 fix switches interrupt handling
2020-08-17 change STEP, DIR, MSx pins state on ENABLE_MOTOR_UC changes
2020-08-19 add STEP event generation to STEP_STATE register handling
2020-08-19 add DIR event generation on register change
2020-08-19 basic single and long press button detection
2020-08-20 update long press detection
2020-08-20 add reset button handling
2020-08-20 rename variable to be more representative
2020-08-20 fix registers types
2020-08-20 add initial protocol support (number of steps + period)
2020-08-20 prevent button press to add extra steps to protocol
2020-08-20 add support for starting/stopping protocol on DI0_CONF option DI0_RISE_START_PROTOCOL
2020-08-20 move DIR pin output change to DIR_STATE register
2020-08-20 update project files
2020-08-24 fix counter type issue
2020-08-24 fix switches interrupt
2020-08-24 fix missing 1 step from protocol
2020-08-24 add common uptime variable for STEP
2020-08-24 minor refactoring
2020-08-24 move BUF_EN handling to the interrupt of EN_DRIVER_UC
2020-08-24 update code with removal of ENABLE_MOTOR_UC
2020-08-24 enable motor if disabled on STEP
2020-08-26 clear STEP_STATE register on clear_step
2020-08-26 update single and long press detection
2020-08-26 fix default values on button press interrupt
2020-08-26 update variables types and remove unused variable
2020-08-26 fix for button long press release detection
2020-08-27 update counters types
2020-08-27 simplify condition
2020-08-27 pressing button for opposite direction of reset will stop resetting
2020-08-27 add switch flags
2020-09-07 add support for disabling motor after a period of inactivity
2020-09-07 change default protocol values
2020-10-09 fix STEP event to generate events also on clear
2020-10-30 fix variable name
2020-10-30 fix switches interrupt handling and event triggering
2020-11-04 fix switch interrupt that might not be triggered when releasing the switch
2020-11-06 remove ugly fix for switches (hardware solution was added)
2020-11-06 fix clear digital outputs
2020-11-06 motor is only turned off on inactivity on microcontroller mode
2020-11-06 fix bug with wrong digital output data on switch press
2020-11-06 change EN_DRIVER_UC interpretation (hw change)
2020-11-09 fix issue with steps only working in one direction after a switch is active
2020-11-09 prevent long press on same direction of active switch
2020-11-17 update switches related variables on start
2020-11-17 update usage of switch_pressed function
2020-11-17 remove unnecessary variable
2020-11-17 rename reset protocol function
2020-11-17 update project config
2020-11-23 [gui] startup project initial commit
2020-11-23 [gui] add Open Sans font to project
2020-11-23 [gui] add Svg support package
2020-11-23 [gui] add basic app header
2020-11-23 [gui] add Bonsai.Harp and System.IO.Ports dependencies
2020-11-26 [gui] add Reactive.Fody dependency
2020-11-26 [gui] update ports list and connect button visibility
2020-12-15 [gui] make use of ReactiveObject and ReactiveWindow base classes
2020-12-15 [gui] add Serilog basic configuration for File and Trace
2020-12-16 [gui] add validation to Configuration fields
2020-12-22 [gui] add Bonsai.Harp preview for net standard dependency
2020-12-22 [gui] get device name when connecting to device
2020-12-22 [gui] add initial support to save configuration to device
2021-01-04 [gui] add device info properties and registers to viewmodel
2021-01-04 [gui] update UI with device information
2021-01-04 [gui] add Reset configuration functionality
2021-01-04 [gui] add Save configuration functionality
2021-01-08 [gui] Update ResetConfiguration to be non-blocking
2021-01-08 [gui] Update ConnectAndGetBaseInfo to be non-blocking
2021-01-13 [gui] update UI text and colors
2021-01-13 [gui] update SaveConfiguration to be non-blocking
2021-03-11 [gui] update version presentation
2021-03-11 [gui] update avalonia dependencies to 0.10.0
2021-03-11 [gui] update version
2021-03-11 [fw] fix issue with initial state of switches detection
2021-03-11 [fw] fix direction on long button press
2021-03-11 [fw] fix initialization on boot while on Arduino mode
2021-03-17 [fw] add new event and board type registers
2021-03-17 [fw] send event on protocol start and end
2021-03-17 [fw] update registers.xls
2021-03-17 [gui] add new registers
2021-03-17 [gui] add support for protocol state event
2021-07-29 [fw] change pin type for arduino mode
2021-08-05 [fw] fix issue with long press not working when a switch is pressed
2021-08-05 [fw] remove variables duplication
2021-08-05 [fw] remove unnecessary code
2021-08-16 [fw] send DIR event on every change and not depend on enabled motor
2021-08-16 [fw] fix switch pressed initial state on boot
2021-08-16 [fw] update firmware version
2021-11-26 [fw] update registers.xls with Protocol Direction
2021-11-26 [fw] add Protocol Direction register
2021-11-26 [fw] update direction when running and stopping the protocol
2021-11-26 [fw] update how the protocol is activated when triggered by the DI0
2021-11-26 [fw] fix issue when starting protocol if the switches are pressed
2021-11-26 [fw] fix issue with steps beings allowed when the switches are pressed
2022-01-04 Added pump board design files and BOM
2022-02-04 [fw] add helper functions
2022-02-04 [fw] add switches debounce
2022-02-04 [fw] allow protocol state to be changed on the register code
2022-09-01 Squashed commit of the following:
    commit f700bba01e987fa5e4db1dd9f613afa1c31fee5c
    Merge: 5d666ed 6e78613
    Author: Luís Teixeira <micboucinha@gmail.com>
    Date: Fri Feb 4 13:14:21 2022 +0000
    Merge branch 'release/fw0.5'
    commit 6e786132b71c56ce7b7231c306ae5543d8e7abee
2022-09-01 Add CAD files
2022-09-06 [gui] add MessageBox when a Harp device other than the Pump is connected
2022-09-06 [gui] update validation limits
2022-09-06 [gui] update project dependencies
2022-09-06 [gui] add copyright and application icon to project
2022-09-06 [gui] add Start Protocol button
2022-09-06 clean up unused code
2022-09-06 [gui] small ui update
2022-09-06 [gui] add Avalonia DevTools
2022-09-06 [gui] create Actions section
2022-09-06 [gui] add nsis build script
2022-09-06 add ProtocolDirection
2022-09-06 [gui] update README
2022-09-06 [gui] resize windows automatically to contents
2022-09-06 [gui] update packages versions
2022-09-06 [gui] copy icon on publish
2022-09-22 [gui] update dependencies
2022-09-22 [gui] update NSIS build script
2022-09-22 [gui] move Device.Pump.GUI to its own folder
2022-09-22 [gui] add Device.Pump main project
2022-09-22 [gui] update projects output folders
2022-09-22 [gui] update namespaces for projects
2022-09-22 [gui] clean up project structure
2022-09-22 [gui] update Bonsai.Harp dependency version
2022-09-23 [gui] update dependency
2022-09-23 [gui] add logs to Device.Pump
2022-09-23 [gui] format files
2022-09-23 [gui] move custom ExceptionHandler to main project
2022-09-28 [gui] create Icons.axaml for styles
2022-09-28 [gui] update images on buttons to use Resources
2022-09-28 [gui] update namespace usage
2022-09-28 [gui] format code
2022-09-28 [gui] update save configuration button
2022-09-29 [gui] update flow rate validation
2022-09-29 [gui] fix typo
2022-09-30 [gui] update connection and initial loading of device information
2022-10-04 [gui] simplified observer creation
2022-10-04 [gui] removed unnecessary validation
2022-10-04 [gui] reformat code
2023-03-15 [gui] move starting of app to the supporting assembly
2023-03-15 [gui] update dependencies and output locations
2023-03-15 [gui] add missing DeviceConfiguration class
2023-03-15 [gui] update default startup screen location
2023-03-15 [gui] allow to change to dark theme
2023-03-15 [gui] update logo on theme change
2023-03-15 [gui] fix issue with IDE plugin for Avalonia
2023-03-15 [gui] assign default application name
2023-03-16 [gui] fix build on MacOS to have native menu and an icon on publish
2023-03-24 [gui] extend client are to include the titlebar
2023-03-27 [gui] update GUI presentation on Linux and Mac
2023-03-27 [gui] improve Windows installer
2023-03-30 [gui] update Avalonia.Svg.Skia dependency
2023-03-30 [gui] add platform logos
2023-03-30 [gui] add new icon resource
2023-03-30 [gui] remove Bluetooth devices from list on Mac
2023-03-30 [gui] prevent window resize
2023-03-30 [gui] update HarpMessages logs presentation and allow to clear log
2023-04-03 [gui] fix issues on About window
2023-04-03 [gui] update local logs folder
2023-04-03 [gui] associate About dialog to NativeMenu
2023-04-03 [gui] update gui version
2023-04-12 Add temporary user folders to gitignore
2023-04-12 Add initial README
2023-04-12 Restructure repository
2023-04-12 Add first version of device schema
2023-04-12 Add automatic generators for Bonsai interface
2023-04-12 Add License to Interface
2023-04-12 Add `preview` tag to package version
2023-04-19 Add licenses
2023-04-19 Rename licenses
2023-04-24 Fix gitignore
2023-04-24 Update schema for consistency across harp ecosystem
2023-04-24 Rename GUI directory to App
2023-04-24 Refactor address and mask name
2023-04-25 Use `StepMode`
2023-04-25 Update Device classes to latest schema
2023-04-25 Add missing package metadata
2023-04-25 Align namespaces with repository naming schema
2023-06-10 Update schema for consistency across devices
2023-06-10 Update `Device` classes to new schema
2023-06-10 Increment release
2023-06-12 Update WhoAmI in the `Device` class
2023-06-12 Up preview release
2023-06-21 Remove space from application name
2023-06-22 Update device id and firmware version
2023-06-23 Update project and installer build file
2023-06-29 update registers - remove aux notes
2023-07-31 Update interface to use new generators
2023-08-03 Add missing package metadata for stable release
2023-08-22 Update start core parameters
2023-08-24 Improve external protocol triggering
2023-08-24 Increase firmware version
2023-08-24 Rename project solution
2024-07-24 Add citation extension
2024-07-24 Update yml - fix masks
2024-07-24 Update autogen interface
2024-11-13 Correct OUT00 limit switch wrong toggling
2024-11-13 Update package metadata, version and add library package
2024-11-13 Update generators and regenerate interface
2024-12-20 Clean code
2025-05-02 Update .gitignore for App
2025-05-03 Move assets to new locations
2025-05-03 Update app dependencies
    This includes updates to .NET 8 (current LTS) and Avalonia version.
2025-05-03 Add new Controls, Converters and Styles
2025-05-03 Update device View and ViewModel to use the Harp interface
    ViewModel changes include events related properties updating periodically.
    View includes reorganization of UI layout to include the available Harp
    interface properties.
2025-05-03 Update project related files
2025-05-03 Remove unneeded files
2025-05-05 Remove unnecessary call from GenerateEventMessages
